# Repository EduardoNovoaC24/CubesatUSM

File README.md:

# CubeSat - Ground Station

## Desde cualquier PC con Chrome

Abre [CubeSat - Ground Station](https://eduardonovoac24.github.io/CubesatUSM/) en Chrome de escritorio. Conecta el Pico LoRa por USB, pulsa **Conectar Pico LoRa** y selecciona su puerto. La página conserva las pestañas de radar ADS-B, telemetría, calibración y control, gráficos, misión y paneles solares de la estación local.

El radar recibe las tramas ADS-B que lleguen por LoRa. Si tienes el STM32 conectado por ST-LINK, usa **Conectar ST-LINK ADS-B** para leer también ese puerto.

El selector **Galaxia** cambia entre azul y morado, rojo y verde. Las transiciones y la formación del cubo respetan la preferencia de movimiento reducido del sistema.

La web estática usa Web Serial y ejecuta en el navegador los mismos analizadores Python del panel local. La primera conexión carga Pyodide desde su CDN. Para regenerar `docs/`, ejecuta `python ground_station/build_pages.py`. GitHub Pages publica `/docs` de la rama `main`.

## Panel local con gráficos y radar

### Azimut y el lote de frenado

En **Prueba 1 · Detumbling**, arma el ESC con el montaje quieto. Cuando el cuerpo esté girando, pulsa **Frenar giro del CubeSat**. La prueba registra la velocidad inicial del cuerpo y el tiempo hasta bajar de 5 rpm por primera vez, además del tiempo de estabilización. Los valores reglamentarios de 60 rpm iniciales y 5 rpm están sujetos a confirmación. La rueda tiene sus propias RPM, que se muestran por separado.

En **Prueba 2 · Azimut por luz**, introduce el azimut inicial de la cara 1. Con los cuatro sensores válidos y el montaje en reposo puedes **Medir sin mover la rueda**, o puedes armar y usar **Seguir luz en Z**. La vista 3D utiliza el giro integrado que informa el STM32 durante el seguimiento. Arrastrar la vista cambia la cámara. Si introduces una referencia independiente del jurado, el panel calcula la menor diferencia angular y muestra el umbral de error correspondiente.

Actualiza el firmware del STM32 y usa un Pico compatible con `BENCH_ARM`, `RUNS` y `RESULTS`. En **Azimut**, aplica el eje y la polaridad de la rueda. El STM32 recupera el sesgo del giroscopio que esté guardado en FLASH o lo calcula automáticamente al detectar una ventana de reposo. Si hay calibración magnética válida, el filtro incorpora el magnetómetro automáticamente cuando recibe una muestra válida. Los ajustes manuales siguen disponibles en **Calibración avanzada y memoria**.

**Iniciar** selecciona el perfil bidireccional y arma el ESC directamente. Conserva el armado mientras recibe tráfico LoRa y medidas válidas del giroscopio. La prueba manual de 30 segundos sigue disponible en sus controles.

En **Prueba 1**, elige un PWM de 1505 a 1575 µs (niveles +1 a +15) y pulsa **Generar 20 pruebas**. Antes de cada frenado, el firmware mantiene el PWM elegido durante 2 segundos. Luego usa el giroscopio del eje seleccionado para compensar el giro. Registra el tiempo hasta la primera entrada en ±0,5 °/s, siempre que se mantenga dentro durante 2 segundos. El gráfico muestra las repeticiones válidas y destaca la más rápida.

Si el PWM no produce giro medible o el montaje no vuelve al reposo entre repeticiones, se interrumpe el lote y se conservan las mediciones válidas. **Cancelar y desarmar** detiene la tanda. Mantén abierta la pestaña que inició el lote para consultar el progreso y mantener el enlace.

### Iniciar el servidor Python

La carpeta `ground_station/` conserva el servidor y el panel original para gráficos, radar ADS-B y telemetría detallada. Sustituye los puertos de ejemplo por los que aparecen en tu PC.

```powershell
py -m pip install pyserial
py ground_station/radar_stm32.py --list-ports
py ground_station/radar_stm32.py --port COM15 --pico-port COM8
```

Abre <http://localhost:8765>. Puedes omitir `--port` si solo usarás el Pico. Cierra el panel local antes de abrir ese mismo puerto desde Chrome.

## Compartir una radio en la misma red

En el PC que tiene el Pico por USB, abre la web y pulsa **Conectar Pico LoRa**. Al abrir el puerto se habilita **Modo servidor**. Introduce el COM y la IPv4 del adaptador de red (puedes consultarla con `ipconfig`), pulsa **Liberar USB y preparar comando**, y copia el comando a PowerShell desde la carpeta del repositorio. Cuando la terminal confirme el arranque, pulsa **Abrir panel LAN**.

También puedes iniciar el servidor directamente desde la terminal si el Pico está libre. Sustituye el COM y la IPv4 del ejemplo por los valores de tu PC.

```powershell
py ground_station/radar_stm32.py --pico-port COM8 --lan-ip 192.168.1.23
```

Ambos abren la URL que imprime la terminal, por ejemplo `http://192.168.1.23:8765`. Si Windows pregunta por el firewall, autoriza Python en redes privadas. La telemetría está disponible en la red local. Para enviar comandos, cada operador escribe su nombre y la clave temporal que aparece en la terminal del anfitrión.

Prueben primero con `PING` y comprueben que ambos ven el mismo `ACK`. El primer comando que modifica el equipo reserva el turno durante 60 segundos de inactividad. `MAG_START` lo reserva durante 125 segundos para cubrir la calibración. El operador puede soltarlo desde el panel. Consultas de estado y `WHEEL STOP` no necesitan el turno, pero sí la clave de mandos.

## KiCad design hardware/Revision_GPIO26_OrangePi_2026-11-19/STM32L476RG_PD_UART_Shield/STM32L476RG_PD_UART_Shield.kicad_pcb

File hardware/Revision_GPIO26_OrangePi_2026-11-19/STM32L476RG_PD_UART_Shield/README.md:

# Orange Pi Zero LTS - acoplamiento directo GPIO26 - 19 noviembre 2026

J7 ya no es un JST UART de tres polos. Es un zocalo hembra THT de 2x13 contactos, paso 2.54 mm, situado en la posicion del GPIO26 del STEP suministrado. Se mantienen activos solo pin 6 GND, pin 8 TX Orange Pi hacia RX STM32 y pin 10 RX Orange Pi desde TX STM32. Los otros 23 contactos quedan sin conexion, incluidos 3.3 V y 5 V. La Orange Pi necesita alimentacion independiente.

## Geometria

Se extrajeron del STEP los 26 centros, el pad cuadrado y los cuatro agujeros M3. Los 26 contactos de J7 coinciden con la proyeccion del modelo, sin escalar el paso. Pin 1 de J7: X=29.845 mm, Y=52.444563 mm, referido al origen superior izquierdo de la shield. Los impares avanzan hacia +X en la fila inferior; los pares estan 2.54 mm hacia arriba. El pin 1 se marca con pad cuadrado.

El modelo tiene separacion entre centros M3 de 42.110914 x 40.110918 mm, ligeramente distinta del nominal 42x40 anterior. H5-H8 se desplazaron unos 0.055 mm por eje para usar la misma referencia geometrica que J7. Mantienen taladro NPTH de 3.2 mm y envolvente de herraje prevista de 7 mm. H1-H4, de 5 mm para la estructura CubeSat, se conservan en sus posiciones anteriores provisionales. Ver ORANGEPI_MONTAJE.csv y MONTAJE_COORDENADAS.csv.

La cara de componentes del STEP esta orientada hacia -Z; se aplico una rotacion coherente para obtener la vista superior de la placa montada. La transformacion y comprobacion de todos los centros estan en reports/STEP_ALIGNMENT.json. El STEP es una referencia CAD suministrada por el usuario y no sustituye una comprobacion dimensional de su unidad fisica.

## Acoplamiento

J7 se instala como hembra en la cara superior de la shield. Los pines macho de Orange Pi deben sobresalir por su cara inferior, hacia la shield, manteniendo la cara de componentes de Orange Pi arriba. Si el cabezal actual tiene los pines largos hacia arriba, no enchufara directamente en esta disposicion: se necesita la orientacion de cabezal correspondiente. No invertir la placa para compensarlo sin revisar el pinout.

Elegir la altura de los cuatro separadores M3 para que coincida con la distancia entre placas del conector realmente acoplado. No fijar una altura arbitraria ni forzar la placa con los tornillos. Revisar pines auxiliares de 13 contactos, USB, Ethernet, microSD y herraje. Se conservaron esos conectores solo como elementos del modelo de referencia; no se añaden conectores electricos para ellos en esta shield.

## Trazado y comprobaciones

Se retrazaron TX/RX y el ramal GND hacia J7. Tres segmentos GND se desplazaron localmente para dejar entrada por B.Cu al pad de PA10. Los circuitos de fotodiodos y asignaciones STM32 se conservan. Total: 85 segmentos, 4 vias metalizadas de 1.0/0.4 mm, 84.0% de longitud de pistas en B.Cu. Las tres conexiones de J7 salen de sus pads por B.Cu.

ERC: 0 errores y 0 advertencias. DRC con paridad: 0 errores, 8 advertencias anteriores de diferencias con biblioteca, 0 conexiones pendientes y 0 problemas de paridad. Informes actuales: reports/ERC_GPIO26.rpt y reports/DRC_GPIO26.rpt. Verificacion de pinout, NC y capas: reports/GPIO26_CHECK.json. Los informes de versiones previas estan en reports/history_pre_gpio26.

CAPAS_Y_SOLDADURA.pdf contiene plano 1:1 de montaje, esquematico actualizado y vistas B.Cu inferior espejada y F.Cu superior. Imprimir el plano al 100%, sin ajustar, y contrastarlo con la placa fisica antes de fabricar. No espejar nuevamente la vista inferior.

No se han efectuado pruebas fisicas ni se ha elegido un modelo comercial concreto de socket con altura de acoplamiento. Siguen pendientes las validaciones electricas previas, los valores R1-R4 y el patron CubeSat H1-H4. No es liberacion definitiva de fabricacion. Para soldar solo por debajo se necesitan agujeros metalizados de componentes y vias; los agujeros mecanicos son NPTH.

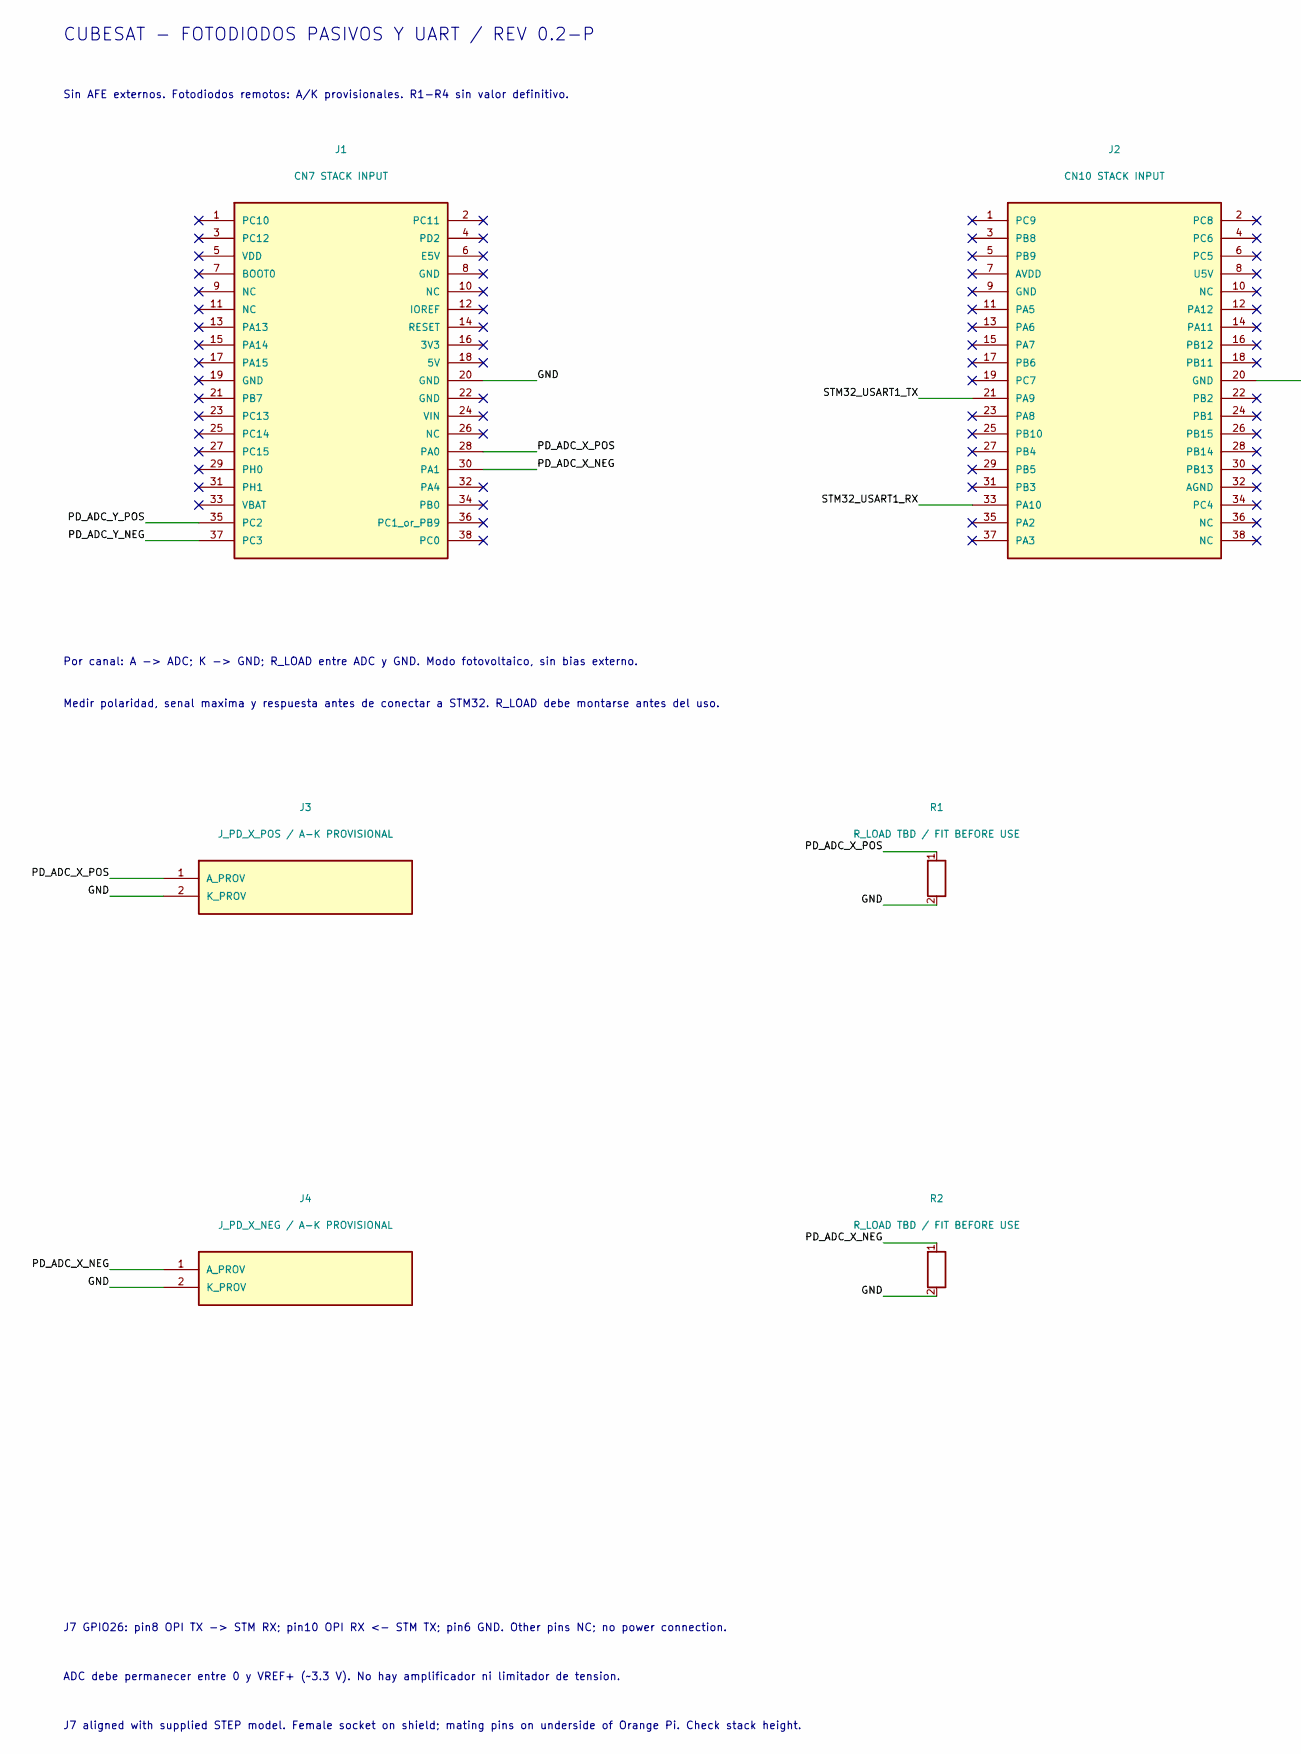
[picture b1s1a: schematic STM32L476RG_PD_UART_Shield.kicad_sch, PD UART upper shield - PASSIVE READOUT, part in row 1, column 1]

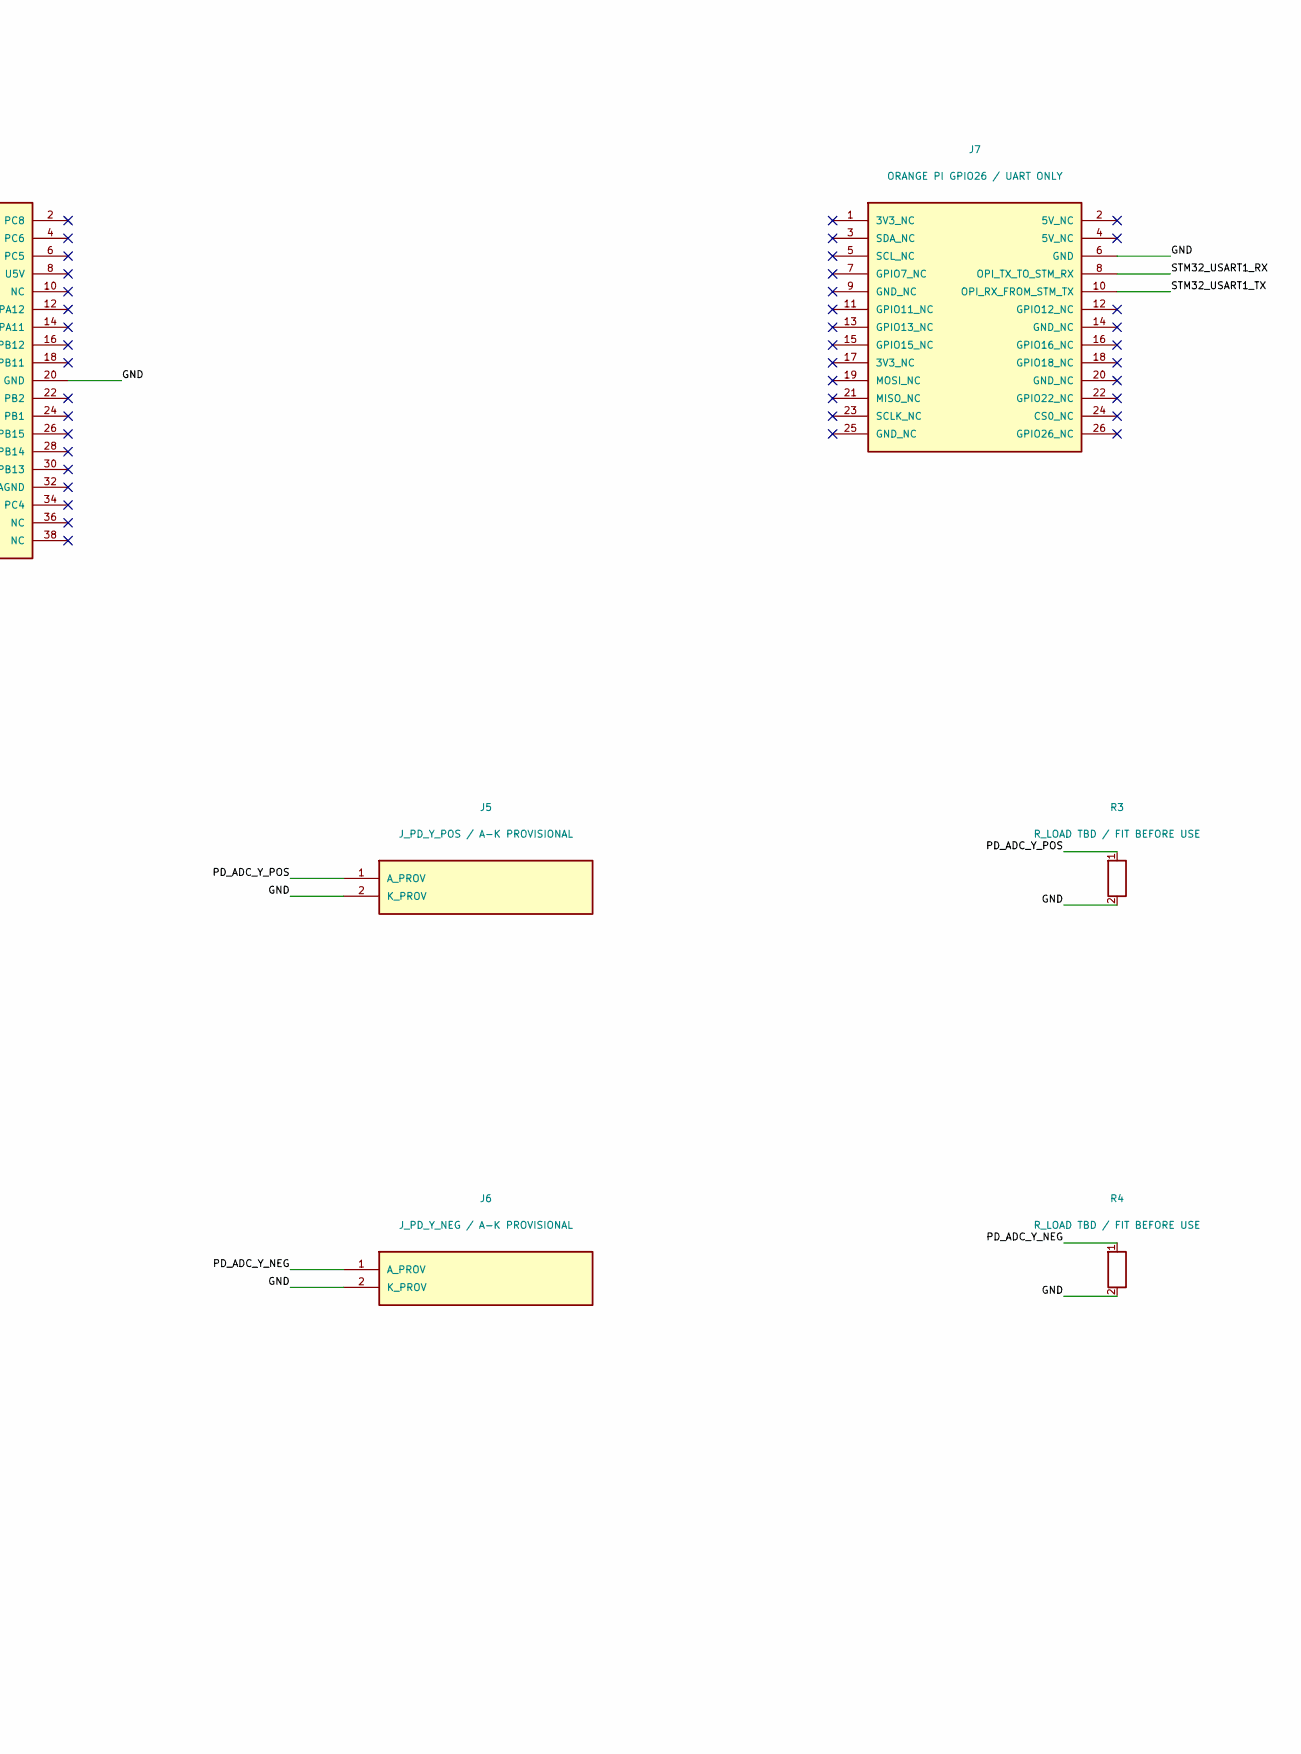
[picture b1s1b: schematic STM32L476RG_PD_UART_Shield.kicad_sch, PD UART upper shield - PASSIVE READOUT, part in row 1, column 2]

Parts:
J1: CN7 STACK INPUT; Morpho_2x19_PTH
J2: CN10 STACK INPUT; Morpho_2x19_PTH
J3: J_PD_X_POS / A-K PROVISIONAL; PD_JST_XA_2
J4: J_PD_X_NEG / A-K PROVISIONAL; PD_JST_XA_2
J5: J_PD_Y_POS / A-K PROVISIONAL; PD_JST_XA_2
J6: J_PD_Y_NEG / A-K PROVISIONAL; PD_JST_XA_2
J7: ORANGE PI GPIO26 / UART ONLY; OPI_GPIO_2x13_SOCKET
R1, R2, R3, R4: R_LOAD TBD / FIT BEFORE USE; R_LOAD_THT

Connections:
/GND: J1.20 (GND), J2.20 (GND), J3.2 (K_PROV), J4.2 (K_PROV), J5.2 (K_PROV), J6.2 (K_PROV), J7.6 (GND), R1.2, R2.2, R3.2, R4.2
/PD_ADC_X_NEG: J1.30 (PA1), J4.1 (A_PROV), R2.1
/PD_ADC_X_POS: J1.28 (PA0), J3.1 (A_PROV), R1.1
/PD_ADC_Y_NEG: J1.37 (PC3), J6.1 (A_PROV), R4.1
/PD_ADC_Y_POS: J1.35 (PC2), J5.1 (A_PROV), R3.1
/STM32_USART1_RX: J2.33 (PA10), J7.8 (OPI_TX_TO_STM_RX)
/STM32_USART1_TX: J2.21 (PA9), J7.10 (OPI_RX_FROM_STM_TX)

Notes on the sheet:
CUBESAT - FOTODIODOS PASIVOS Y UART / REV 0.2-P
Sin AFE externos. Fotodiodos remotos: A/K provisionales. R1-R4 sin valor definitivo.
Por canal: A -> ADC; K -> GND; R_LOAD entre ADC y GND. Modo fotovoltaico, sin bias externo.
Medir polaridad, senal maxima y respuesta antes de conectar a STM32. R_LOAD debe montarse antes del uso.
J7 GPIO26: pin8 OPI TX -> STM RX; pin10 OPI RX <- STM TX; pin6 GND. Other pins NC; no power connection.
ADC debe permanecer entre 0 y VREF+ (~3.3 V). No hay amplificador ni limitador de tension.
J7 aligned with supplied STEP model. Female socket on shield; mating pins on underside of Orange Pi. Check stack height.

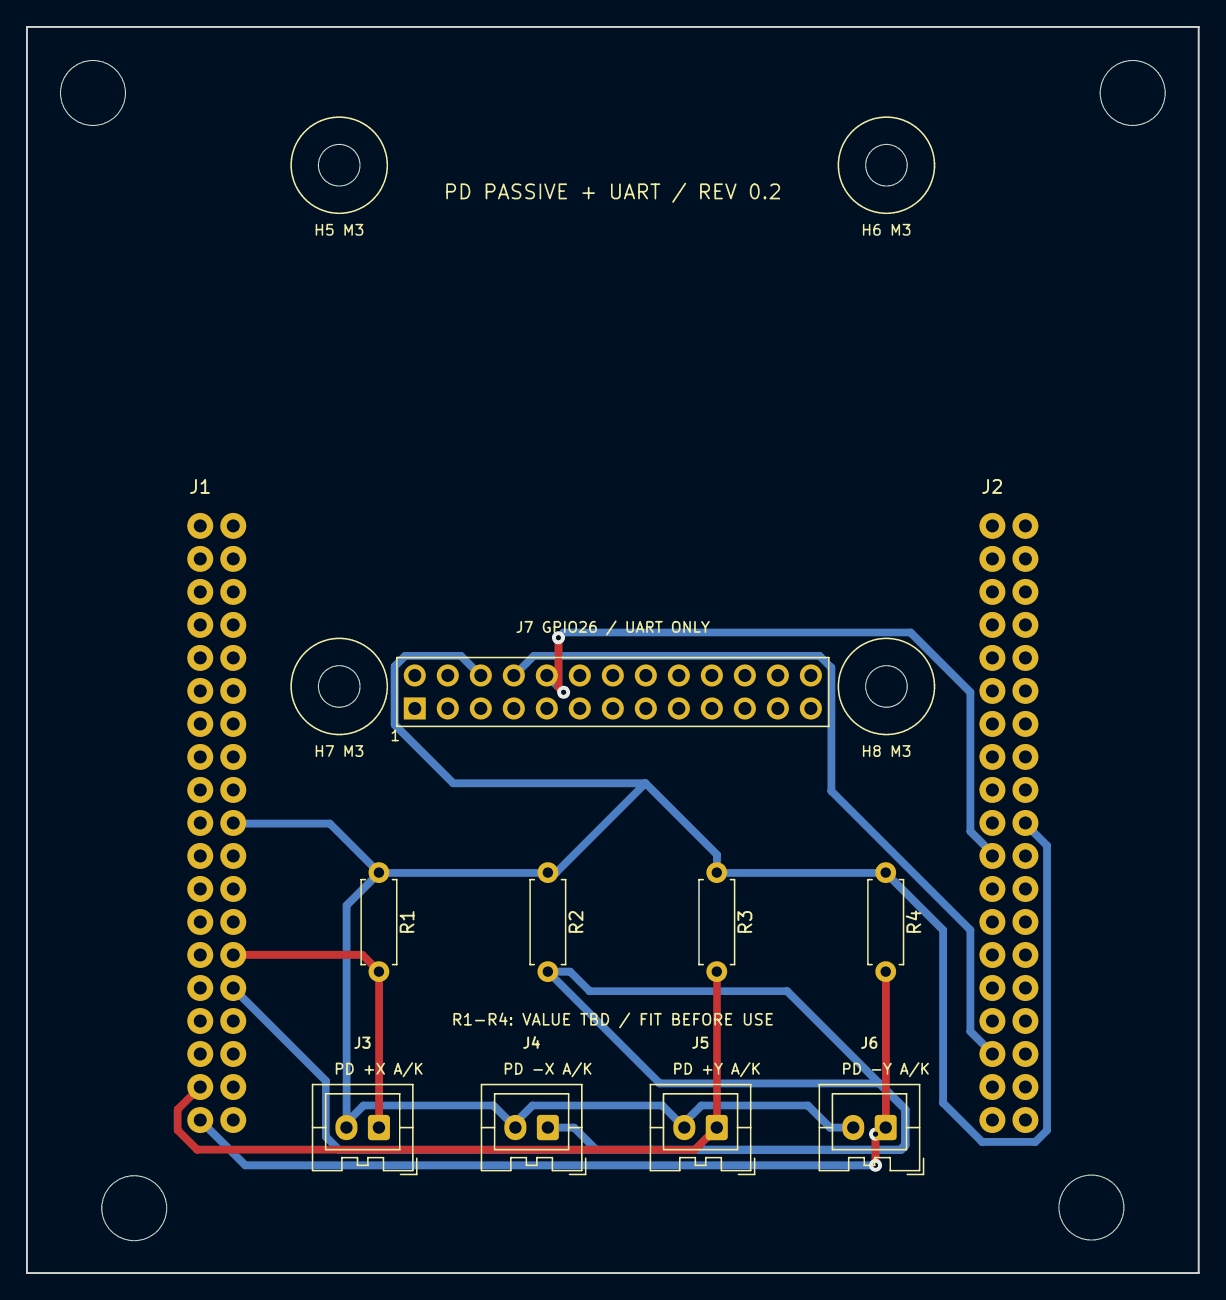
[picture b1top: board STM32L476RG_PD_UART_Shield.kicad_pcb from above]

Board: 2 copper layers, 90.2 x 95.9 mm, 19 parts (0 on the bottom side), 7 nets.

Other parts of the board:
H1, H2, H3, H4: MountingHole_5mm_NPTH
H5, H6, H7, H8: OrangePi_M3_3.2mm_NPTH

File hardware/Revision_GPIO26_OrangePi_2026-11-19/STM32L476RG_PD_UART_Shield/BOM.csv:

References,Quantity,Description,Status
"J1,J2",2,Morpho 2x19 2.54mm THT,Confirmar apilado
"J3,J4,J5,J6",4,JST XA B02B-XASK-1 2p 2.50mm,Carcasa XAP-02V-1 y contactos segun cable
J7,1,"Zocalo hembra 2x13 THT, paso 2.54mm",Acoplamiento directo GPIO26; altura compatible con separadores y pines reales
"R1,R2,R3,R4",4,Resistencia axial DIN0207 P7.62mm THT,"Valor TBD, determinar y montar antes de usar"
H5-H8 hardware,4,Separador M3 hembra-hembra,"Altura segun conjunto real, envolvente maxima 7mm"
OrangePi screws,8,Tornillo M3,"Longitud segun separador y placa, envolvente maxima 7mm"

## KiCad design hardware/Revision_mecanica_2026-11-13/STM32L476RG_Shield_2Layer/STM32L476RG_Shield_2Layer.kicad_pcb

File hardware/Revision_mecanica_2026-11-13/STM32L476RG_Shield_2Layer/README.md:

# Revision mecanica - 13 noviembre 2026

Contorno nominal 90.17 x 95.89 mm. Circuito anterior centrado, sin escalar huellas ni pistas. Cuatro taladros NPTH de 5.00 mm alineados con la otra PCB.

IMPORTANTE: posicion de agujeros provisional. Se asumio fila superior a 5.08 mm del borde y parejas centradas horizontalmente. Confirmar plano antes de perforar. Ver MECANICA_ACTUALIZADA.md y MONTAJE_COORDENADAS.csv.

DRC: 15 infracciones, 6 conexiones pendientes y 11 problemas de paridad. El archivo del escritorio contiene seis huellas adicionales sin referencia y con pads sin red en lugares de conexiones entre capas. Se conservaron estos cambios: no se repararon al ampliar el contorno.

Informe real: reports/DRC_MECANICA.rpt. Los informes anteriores y README_CIRCUITO_ORIGEN.md describen la version de origen; no son una validacion de esta revision. No liberado para fabricacion. Se omitieron exportaciones antiguas de cobre y taladros para evitar confundirlas con el contorno nuevo.

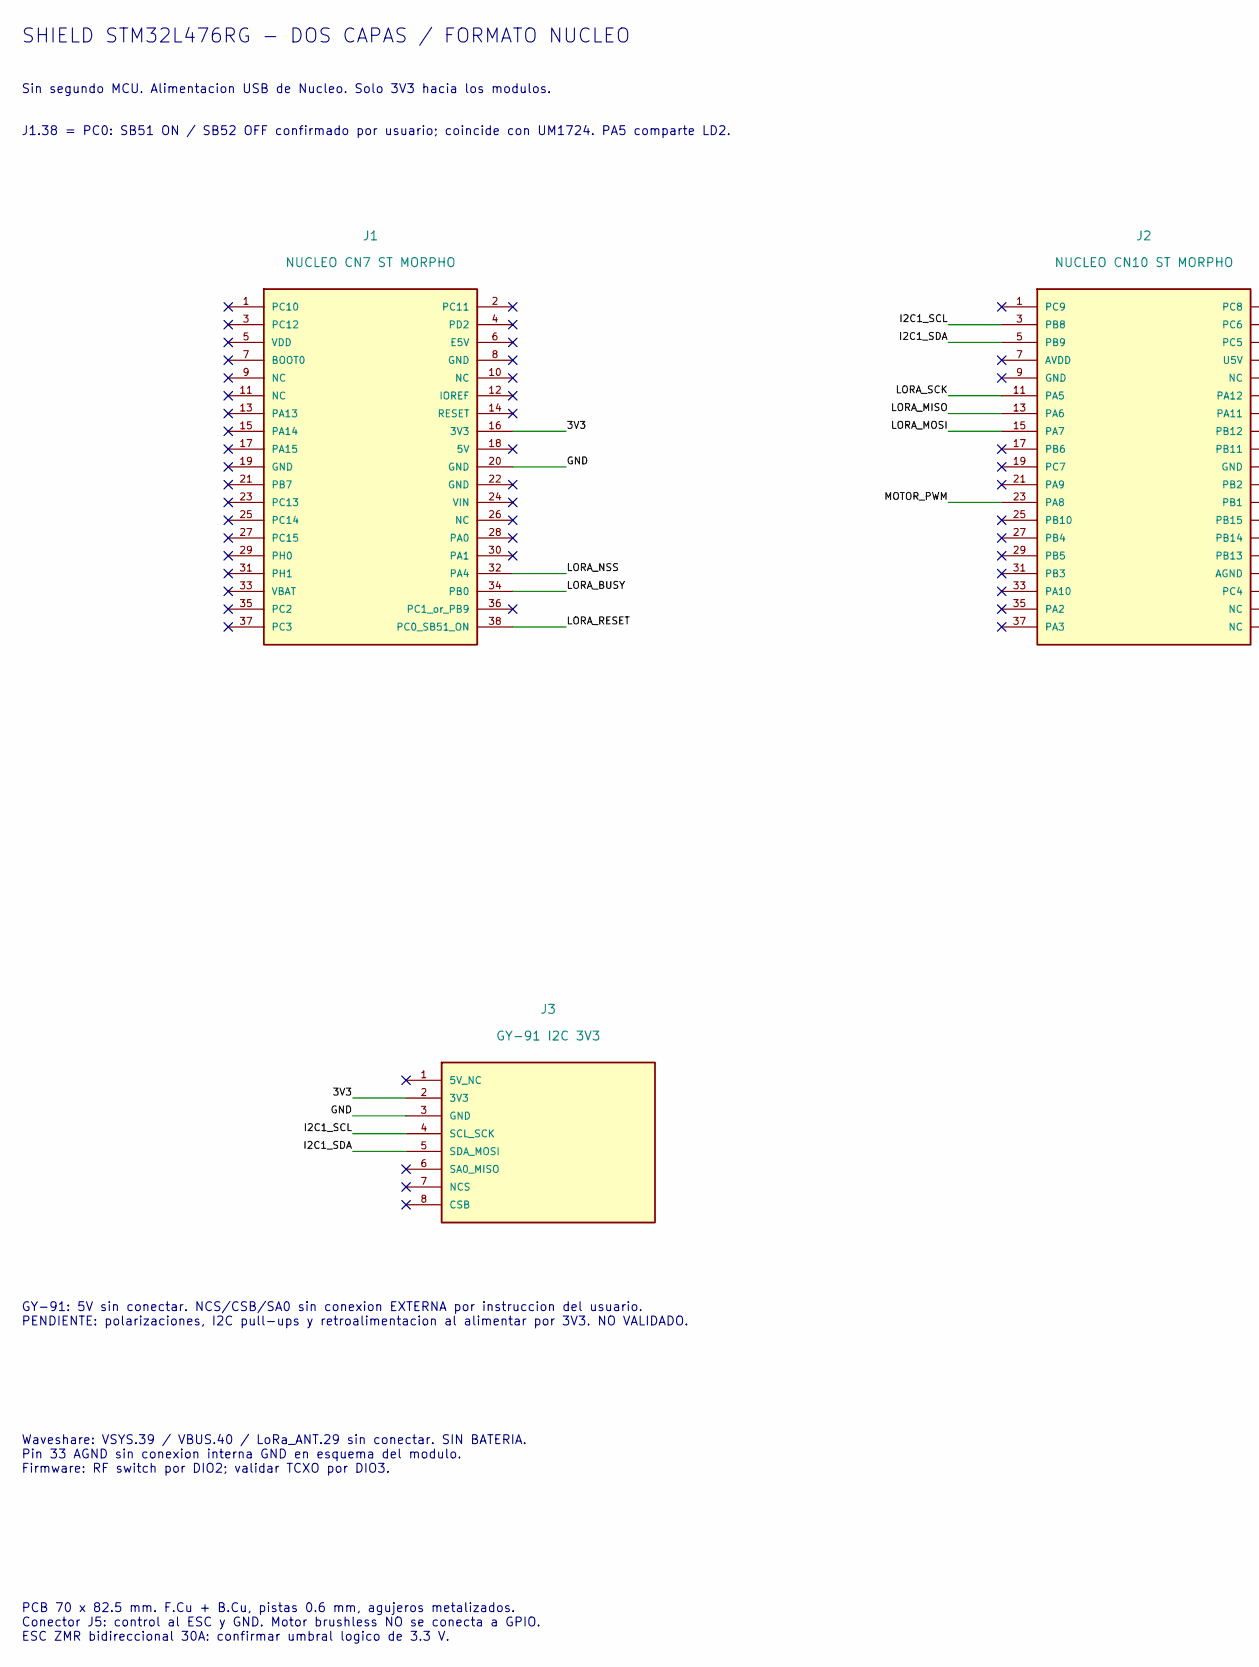
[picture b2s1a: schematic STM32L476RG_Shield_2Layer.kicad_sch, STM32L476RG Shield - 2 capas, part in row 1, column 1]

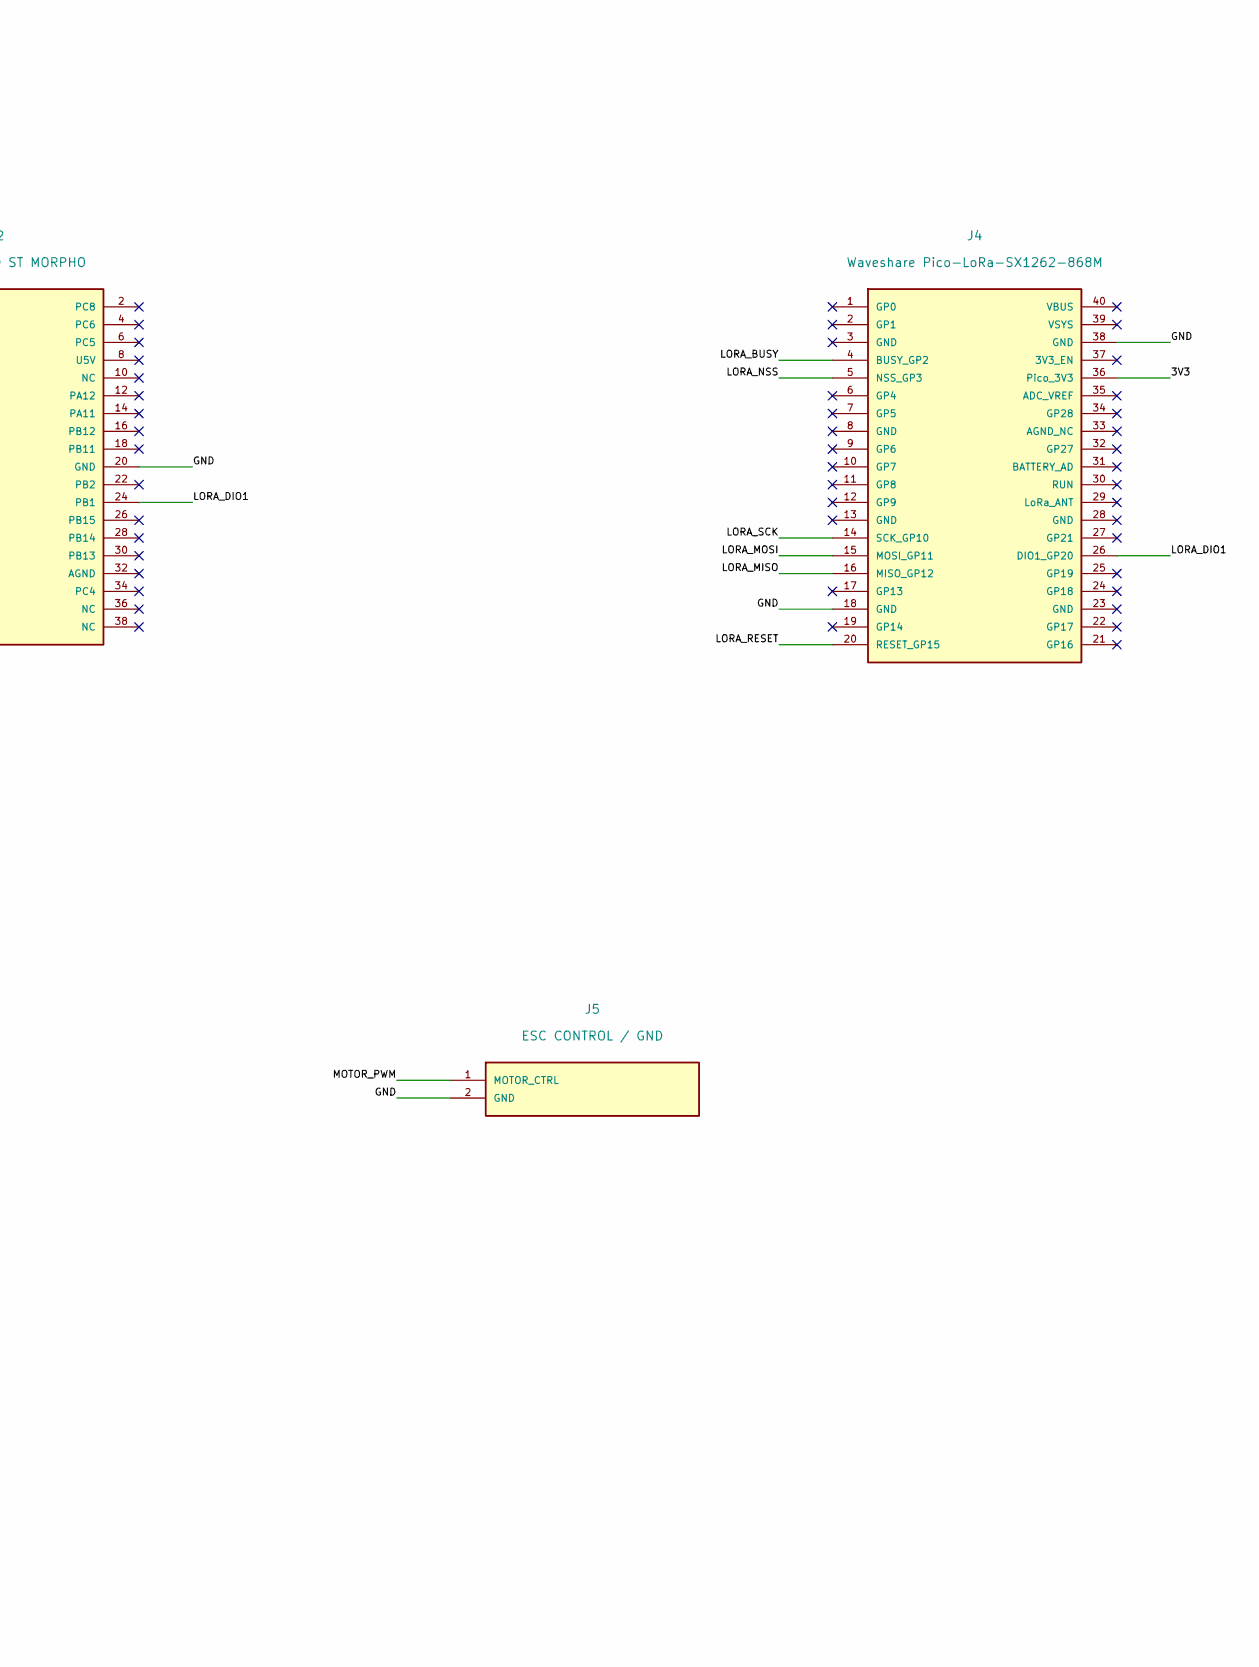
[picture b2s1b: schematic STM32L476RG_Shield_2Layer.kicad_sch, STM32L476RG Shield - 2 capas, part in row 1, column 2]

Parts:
J1: NUCLEO CN7 ST MORPHO; Morpho_2x19_PTH
J2: NUCLEO CN10 ST MORPHO; Morpho_2x19_PTH
J3: GY-91 I2C 3V3; GY91_1x08_PTH
J4: Waveshare Pico-LoRa-SX1262-868M; Waveshare_Pico_40_PTH
J5: ESC CONTROL / GND; ESC_Control_1x02_PTH

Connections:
/3V3: J1.16 (3V3), J3.2 (3V3), J4.36 (Pico_3V3)
/GND: J1.20 (GND), J2.20 (GND), J3.3 (GND), J4.18 (GND), J4.38 (GND), J5.2 (GND)
/I2C1_SCL: J2.3 (PB8), J3.4 (SCL_SCK)
/I2C1_SDA: J2.5 (PB9), J3.5 (SDA_MOSI)
/LORA_BUSY: J1.34 (PB0), J4.4 (BUSY_GP2)
/LORA_DIO1: J2.24 (PB1), J4.26 (DIO1_GP20)
/LORA_MISO: J2.13 (PA6), J4.16 (MISO_GP12)
/LORA_MOSI: J2.15 (PA7), J4.15 (MOSI_GP11)
/LORA_NSS: J1.32 (PA4), J4.5 (NSS_GP3)
/LORA_RESET: J1.38 (PC0_SB51_ON), J4.20 (RESET_GP15)
/LORA_SCK: J2.11 (PA5), J4.14 (SCK_GP10)
/MOTOR_PWM: J2.23 (PA8), J5.1 (MOTOR_CTRL)

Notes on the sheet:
SHIELD STM32L476RG - DOS CAPAS / FORMATO NUCLEO
Sin segundo MCU. Alimentacion USB de Nucleo. Solo 3V3 hacia los modulos.
J1.38 = PC0: SB51 ON / SB52 OFF confirmado por usuario; coincide con UM1724. PA5 comparte LD2.
GY-91: 5V sin conectar. NCS/CSB/SA0 sin conexion EXTERNA por instruccion del usuario. PENDIENTE: polarizaciones, I2C pull-ups y retroalimentacion al alimentar por 3V3. NO VALIDADO.
Waveshare: VSYS.39 / VBUS.40 / LoRa_ANT.29 sin conectar. SIN BATERIA. Pin 33 AGND sin conexion interna GND en esquema del modulo. Firmware: RF switch por DIO2; validar TCXO por DIO3.
PCB 70 x 82.5 mm. F.Cu + B.Cu, pistas 0.6 mm, agujeros metalizados. Conector J5: control al ESC y GND. Motor brushless NO se conecta a GPIO. ESC ZMR bidireccional 30A: confirmar umbral logico de 3.3 V.

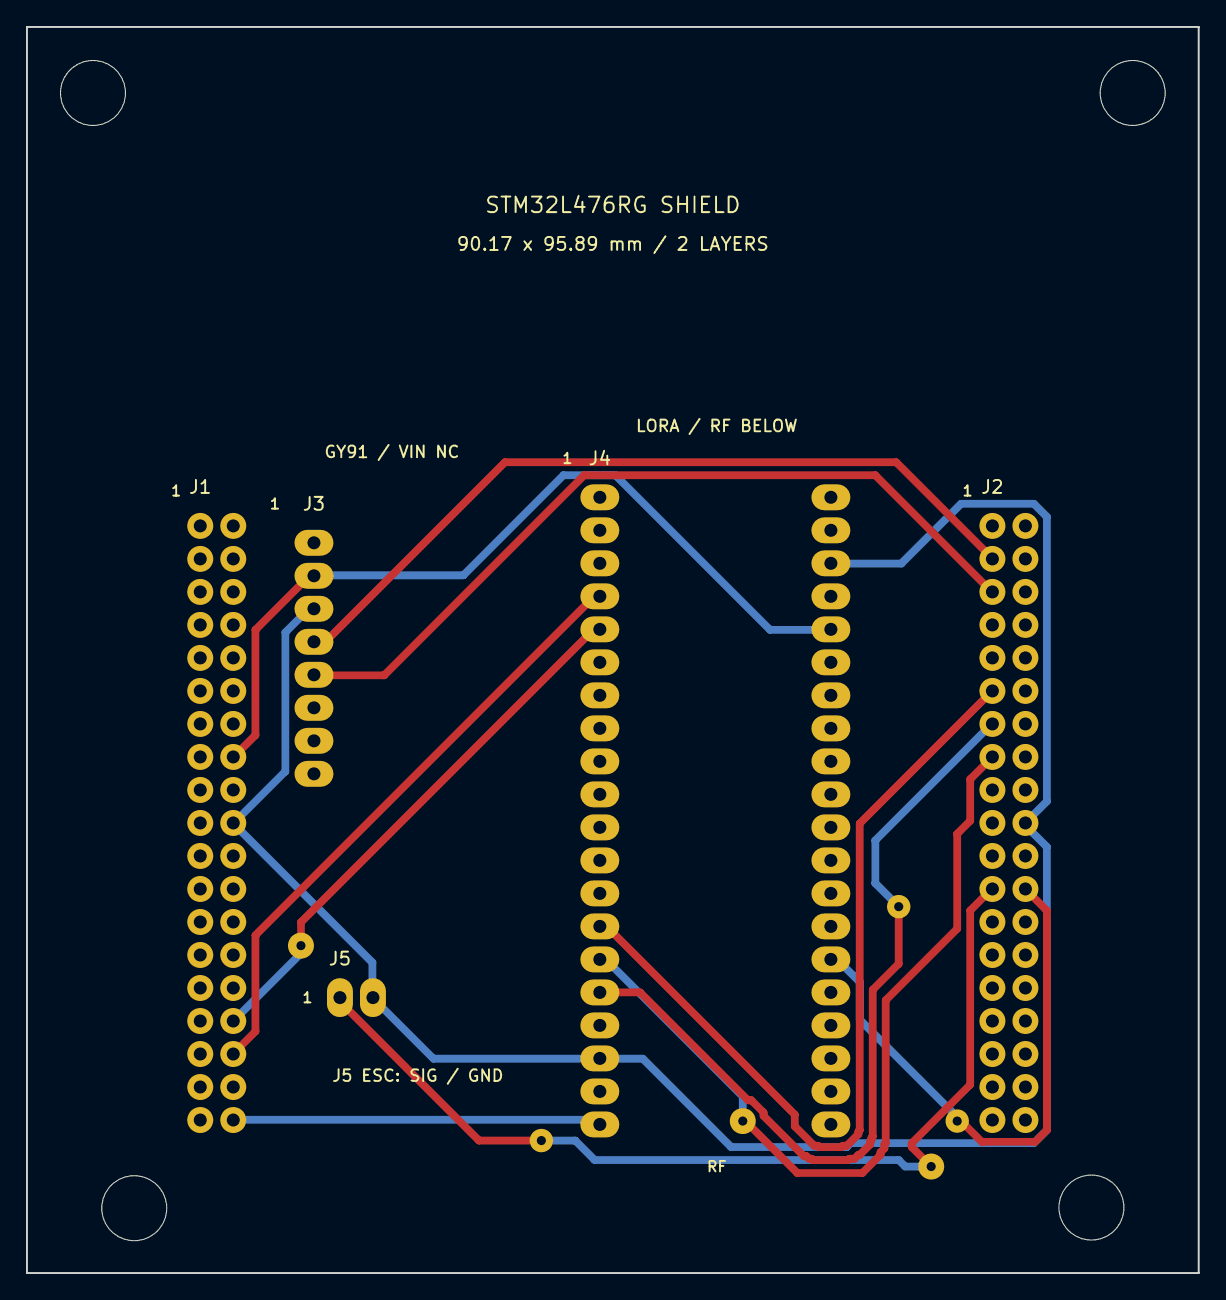
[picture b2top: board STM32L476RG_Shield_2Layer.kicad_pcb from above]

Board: 2 copper layers, 90.2 x 95.9 mm, 9 parts (0 on the bottom side), 12 nets.

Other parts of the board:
H1, H2, H3, H4: MountingHole_5mm_NPTH

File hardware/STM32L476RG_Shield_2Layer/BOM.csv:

Reference,Quantity,Description,Notes
"J1,J2",2,Female socket 2x19 2.54mm THT,Mount below shield; confirm stack height and pin length
J3,1,Female socket 1x08 2.54mm THT,GY91 removable
GY91_HEADER,1,Male pin strip 1x08 2.54mm,Fit to module if not already fitted
J4,2,Male pin strip 1x20 2.54mm THT,Mate to existing Waveshare female sockets
J5,1,Header 1x02 2.54mm THT,Signal and GND to ESC only
GY91_MODULE,1,Purchased GY91 MPU9250 BMP280,Existing module; electrical qualifications still pending
LORA_MODULE,1,Purchased Waveshare Pico-LoRa-SX1262-868M,3V3 at physical pin36; no battery/VSYS/VBUS

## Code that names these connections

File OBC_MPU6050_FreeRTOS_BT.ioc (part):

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Mcu.Name=STM32L476R(C-E-G)Tx
Mcu.Package=LQFP64
Mcu.UserName=STM32L476RGTx
PA10.Mode=Asynchronous
PA10.Signal=USART1_RX
PA13\ (JTMS-SWDIO).Mode=Serial_Wire
PA13\ (JTMS-SWDIO).Signal=SYS_JTMS-SWDIO
PA14\ (JTCK-SWCLK).Mode=Serial_Wire
PA14\ (JTCK-SWCLK).Signal=SYS_JTCK-SWCLK
PA2.Mode=Asynchronous
PA2.Signal=USART2_TX
PA3.Mode=Asynchronous
PA3.Signal=USART2_RX
PA4.GPIOParameters=GPIO_Label,PinState
PA4.GPIO_Label=SX1262_NSS
PA4.PinState=GPIO_PIN_SET
PA4.Signal=GPIO_Output
PA5.Mode=Full_Duplex_Master
PA5.Signal=SPI1_SCK
PA6.Mode=Full_Duplex_Master
PA6.Signal=SPI1_MISO
PA7.Mode=Full_Duplex_Master
PA7.Signal=SPI1_MOSI
PA8.Signal=S_TIM1_CH1
PA9.Mode=Asynchronous
PA9.Signal=USART1_TX
PB0.GPIOParameters=GPIO_Label
PB0.GPIO_Label=SX1262_BUSY
PB0.Signal=GPIO_Input
PB1.GPIOParameters=GPIO_Label
PB1.GPIO_Label=SX1262_DIO1
PB1.Signal=GPXTI1
PB8.Mode=I2C
PB8.Signal=I2C1_SCL
PB9.Mode=I2C
PB9.Signal=I2C1_SDA
PC0.GPIOParameters=GPIO_Label
PC0.GPIO_Label=SX1262_NRESET
PC0.Signal=GPIO_Output
RCC.HSE_VALUE=8000000
RCC.SYSCLKFreq_VALUE=80000000
RCC.SYSCLKSource=RCC_SYSCLKSOURCE_PLLCLK
board=custom
